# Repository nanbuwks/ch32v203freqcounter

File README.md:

# ch32v203freqcounter

form from https://github.com/AKBONE/ch32v003freqcounter

# License

Public Domain ((cc0)
However, libraries used are subject to individual licenses.

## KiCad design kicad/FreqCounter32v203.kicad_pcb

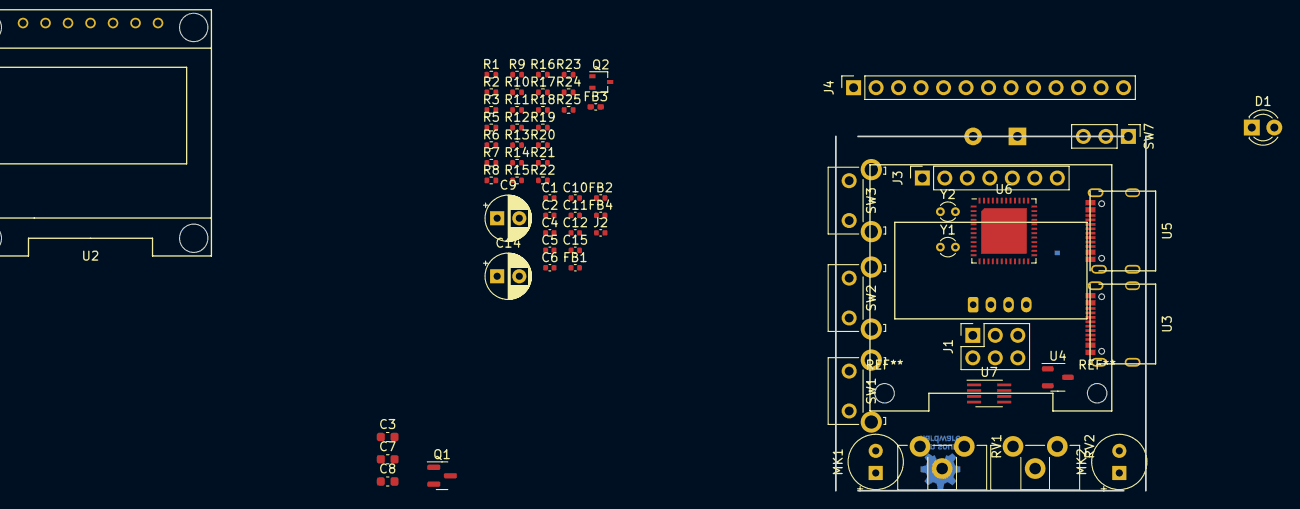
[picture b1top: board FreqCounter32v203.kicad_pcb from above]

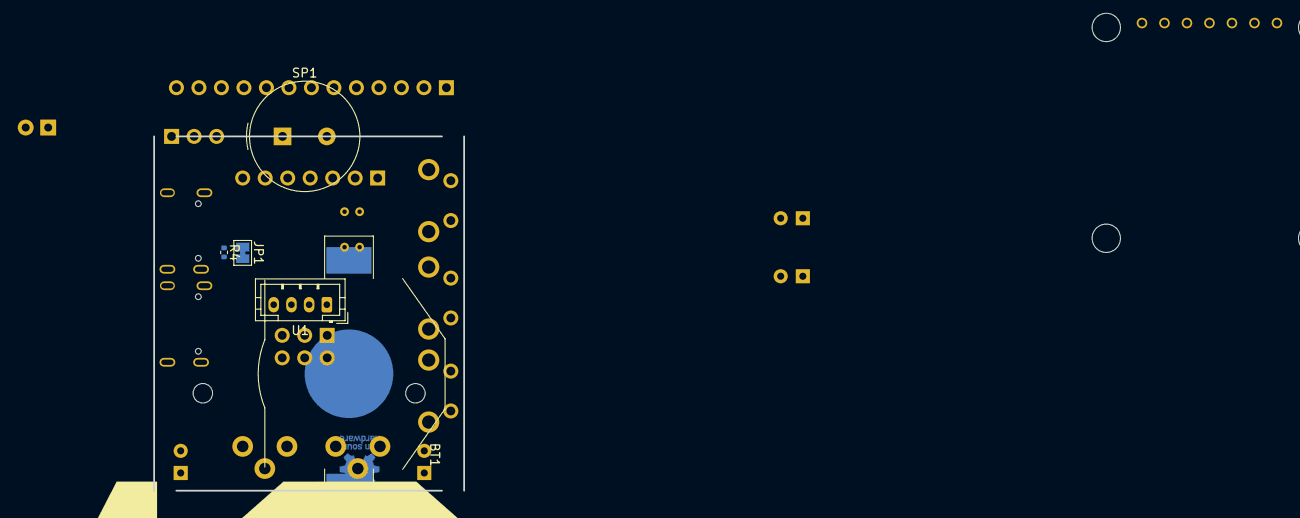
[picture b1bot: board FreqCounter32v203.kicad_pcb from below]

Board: 2 copper layers, 35.0 x 40.0 mm, 70 parts (5 on the bottom side), 65 nets, no tracks yet.

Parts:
BT1: Battery; BatteryHolder_Keystone_3002_1x2032
C1: C; C_0402_1005Metric
C2: 20p; C_0402_1005Metric
C3, C7, C8: 20p; C_0603_1608Metric
C4, C5, C11: 10u; C_0402_1005Metric
C6: 1u; C_0402_1005Metric
C9, C14: 10u; CP_Radial_D5.0mm_P2.50mm
C10, C15: 0.1; C_0402_1005Metric
C12: 0.1u; C_0402_1005Metric
D1: LED; LED_D3.0mm
FB1, FB2, FB4: FerriteBead_Small; C_0402_1005Metric
FB3: FerriteBead_Small; C_0402_1005Metric_Pad0.74x0.62mm_HandSolder
J1: BOOT; PinSocket_2x03_P2.54mm_Vertical
J2: WCH_LINK; C_0402_1005Metric
J3: Conn_01x07_Socket; PinSocket_1x07_P2.54mm_Vertical
J4: AKBONE2024_SOCKET; PinSocket_1x13_P2.54mm_Vertical
JP1: Jumper_2_Bridged; SolderJumper-2_P1.3mm_Bridged_Pad1.0x1.5mm
MK1, MK2: mic; CP_Radial_Tantal_D6.0mm_P2.50mm
Q1: NMOS LX2302S; SOT-23
Q2: PMOS_GSD_RC2101; SOT-323_SC-70
R1: 180Ω; R_0402_1005Metric
R2: 2.7kΩ; R_0402_1005Metric
R3, R4: OPEN; R_0402_1005Metric
R5, R6, R10, R11: 5.1k; R_0402_1005Metric
R7, R12: 1.5k; R_0402_1005Metric
R8, R9, R13, R14: 47; R_0402_1005Metric
R15, R19, R20, R21: 1k; R_0402_1005Metric
R16, R17: 10k; R_0402_1005Metric
R18, R22: 59k; R_0402_1005Metric
R23: 3.3k; R_0402_1005Metric
R24: 12k; R_0402_1005Metric
R25: 4.7k; R_0402_1005Metric
RV1, RV2: 200k; Potentiometer_ACP_CA9-H2,5_Horizontal
SP1: SPEAKER; Buzzer_TDK_PS1240P02BT_D12.2mm_H6.5mm
SW1: OK; SW_SPST_Omron_B3F-315x_Angled
SW2: ↓; SW_SPST_Omron_B3F-315x_Angled
SW3: ↑; SW_SPST_Omron_B3F-315x_Angled
SW7: SWITCH_INV; PinHeader_1x03_P2.54mm_Vertical
U1: SEEED_GROVE; JST_PH_B4B-PH-K_1x04_P2.00mm_Vertical
U2: OLED_0.96in_SPI
U3, U5: USB-C_16PIN; USB_Type_C_16Pin_Female
U4: XC6206PxxxMR; SOT-23-3
U6: CH32C203C8T6; Infineon_MLPQ-48-1EP_7x7mm_P0.5mm_EP5.15x5.15mm
U7: LMV358; SSOP-8_2.95x2.8mm_P0.65mm
Y1: 32M; Crystal_DS15_D1.5mm_L5.0mm_Vertical
Y2: 32.768k; Crystal_DS15_D1.5mm_L5.0mm_Vertical

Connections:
+5V: C5.2, FB3.2, FB4.2, U3.A9 (VBUS), U3.B4 (VBUS), U4.3 (VI), U5.A9 (VBUS), U5.B4 (VBUS)
ACENTER: J4.11, R16.2, R17.1, R20.1, R21.1, U6.12 (PA2/ADC2)
AGND: BT1.2, C4.2, C11.2, C12.2, FB2.2, J4.13, MK1.1 (-), MK2.1 (-), Q2.1 (G), R17.2, R24.1, U6.8 (VSSA), U7.4 (V-)
AVCC: C4.1, C12.1, Q1.3 (S), R15.1, R16.1, R19.1, SW7.2, U6.9 (VDDA), U7.8 (V+)
BATT: BT1.1, J4.12, Q2.3 (D), U6.1 (VBAT)
BOOT0: J1.2, U6.44 (BOOT0)
BOOT1: J1.5, U6.20 (PB2/BOOT1)
CS: J3.7, U2.7 (CS), U6.13 (PA3/ADC3)
DC: J3.6, U2.6 (DC), U6.14 (PA4/ADC4)
GND: C1.2, C2.1, C3.1, C5.1, C6.1, C7.1, C8.1, D1.1 (K), FB2.1, J1.3, J1.4, J3.1, J4.2, R3.2, R5.2, R6.2, R10.2, R11.2, SP1.1, U1.4 (Black/GND), U2.1 (GND), U3.A1 (GND), U3.A12 (GND), U3.B1 (GND), U3.B12 (GND), U4.1 (GND), U5.A1 (GND), U5.A12 (GND), U5.B1 (GND), U5.B12 (GND), U6.23 (VSS_1), U6.35 (VSS_2), U6.47 (VSS_3)
LED: R1.1, U6.40 (PB4)
MIC1: RV1.2, U6.10 (PA0/WKUP/ADC0), U7.1
MIC2: RV2.2, U6.11 (PA1/ADC1), U7.7
MOSI: J3.4, U2.4 (D1), U6.17 (PA7/ADC7)
unnamed: C9.2, C10.1
unnamed: C11.1, R23.1, R24.2, R25.1
unnamed: C14.2, C15.1
unnamed: D1.2 (A), R1.2
unnamed: FB3.1, U3.A4 (VBUS), U3.B9 (VBUS)
unnamed: FB4.1, U5.A4 (VBUS), U5.B9 (VBUS)
unnamed: J2.2, U6.34 (PA13/SWDIO)
unnamed: JP1.2 (B), R4.2, SP1.2
unnamed: C9.1, MK1.2 (+), R15.2
unnamed: C14.1, MK2.2 (+), R19.2
unnamed: C6.2, FB1.2, Q1.1 (D), R25.2, U4.2 (VO)
unnamed: Q1.2 (G), R23.2
unnamed: Q2.2 (S), SW7.1
unnamed: R2.2, R3.1, SW1.1, SW2.1, SW3.1
unnamed: R18.2, RV1.1
unnamed: R22.2, RV2.1
unnamed: U1.2 (White/Dn1/An1/TX/SDA), U6.46 (PB9)
unnamed: U1.1 (Yellow/Dn/An/RX/SCL), U6.45 (PB8)
unnamed: R10.1, U3.A5 (CC1)
unnamed: R11.1, U3.B5 (CC2)
unnamed: R12.1, R13.1, U3.A7 (DN1), U3.B7 (DN2)
unnamed: R14.1, U3.A6 (DP1), U3.B6 (DP2)
unnamed: R5.1, U5.A5 (CC1)
unnamed: R6.1, U5.B5 (CC2)
unnamed: R7.1, R9.1, U5.A7 (DN1), U5.B7 (DN2)
unnamed: R8.1, U5.A6 (DP1), U5.B6 (DP2)
unnamed: C2.2, U6.5 (OSC_IN/PD0), Y1.2
unnamed: C3.2, U6.6 (OSC_OUT/PD1), Y1.1
unnamed: C7.2, U6.3 (PC14/OSC32IN), Y2.2
unnamed: C8.2, U6.4 (PC15/OSC32OUT), Y2.1
unnamed: R18.1, R21.2, U7.2 (-)
unnamed: R20.2, R22.1, U7.6 (-)
OLED_RESET: J3.5, U2.5 (RST), U6.29 (PA8)
OPAMP1: C10.2, J4.9, U7.3 (+)
OPAMP2: C15.2, J4.10, U7.5 (+)
PB10: J4.3, U6.21 (PB10)
PB11: J4.4, U6.22 (PB11)
PB12: J4.5, U6.25 (PB12)
PB13: J4.6, U6.26 (PB13)
PB14: J4.7, U6.27 (PB14)
PB15: J4.8, U6.28 (PB15)
SCK: J3.3, U2.3 (D0), U6.15 (PA5/ADC5)
SPEAKER: JP1.1 (A), R4.1, U6.38 (PA15)
SW1: SW1.2, U6.18 (PB0/ADC8)
SW2: SW2.2, U6.19 (PB1/ADC9)
SW3: SW3.2, U6.39 (PB3)
USB1_DN: R9.2, U6.32 (PA11/USB1DM)
USB1_DP: R8.2, U6.33 (PA12/USB1DP)
USB2_DN: R13.2, U6.42 (PB6/USB2DM)
USB2_DP: R14.2, U6.43 (PB7/USB2DP)
VCC: C1.1, FB1.1, J1.1, J1.6, J2.1, J3.2, J4.1, R2.1, R7.2, R12.2, U1.3 (Red/VCC), U2.2 (VCC), U6.24 (VDD_VIO_1), U6.36 (VDD_2), U6.48 (VDD_VIO_3)

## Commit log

2024-08-29 file delete and rename
2024-10-18 in progress
